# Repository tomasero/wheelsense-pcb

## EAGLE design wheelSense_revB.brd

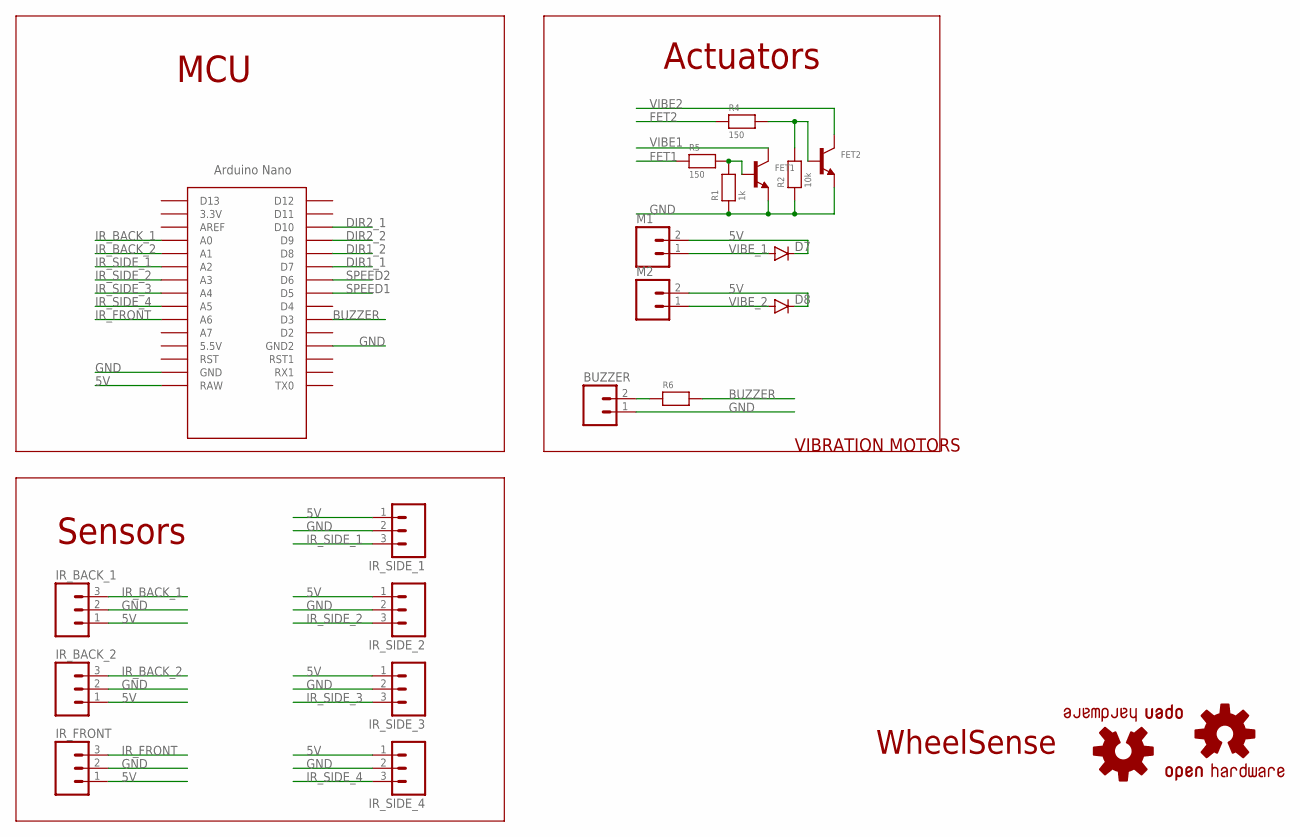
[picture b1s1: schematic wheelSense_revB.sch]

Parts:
BUZZER: M02POLAR; MOLEX-1X2
D7, D8: DIODESOD123; SOD-123
FET1, FET2: TRANSISTOR_NPN; SOT23-R
IR_BACK_1, IR_BACK_2: M03POLAR; MOLEX-1X3
IR_FRONT: M03POLAR; MOLEX-1X3
IR_SIDE_1, IR_SIDE_2, IR_SIDE_3, IR_SIDE_4: M03POLAR; MOLEX-1X3
LOGO1, LOGO2: OSHW-LOGOL-TOP; OSHW_LOGO_L_TOP
M1, M2: M02POLAR; MOLEX-1X2
R1: 1k; 0805
R2: 10k; 0805
R4, R5: 150; 0805
R6: RESISTOR0805; 0805
U$1: NANO

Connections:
5V: D7.C, D8.C, IR_BACK_1.1, IR_BACK_2.1, IR_FRONT.1, IR_SIDE_1.1, IR_SIDE_2.1, IR_SIDE_3.1, IR_SIDE_4.1, M1.2, M2.2, U$1.RAW
BUZZER: R6.2, U$1.D3
DIR1_1: U$1.D7
DIR1_2: U$1.D8
DIR2_1: U$1.D10
DIR2_2: U$1.D9
FET1: R5.1
FET2: R4.1
GND: BUZZER.1, FET1.2 (E), FET2.2 (E), IR_BACK_1.2, IR_BACK_2.2, IR_FRONT.2, IR_SIDE_1.2, IR_SIDE_2.2, IR_SIDE_3.2, IR_SIDE_4.2, R1.1, R2.1, U$1.GND, U$1.GND1 (GND2)
IR_BACK_1: IR_BACK_1.3, U$1.A0
IR_BACK_2: IR_BACK_2.3, U$1.A1
IR_FRONT: IR_FRONT.3, U$1.A6
IR_SIDE_1: IR_SIDE_1.3, U$1.A2
IR_SIDE_2: IR_SIDE_2.3, U$1.A3
IR_SIDE_3: IR_SIDE_3.3, U$1.A4
IR_SIDE_4: IR_SIDE_4.3, U$1.A5
unnamed: BUZZER.2, R6.1
unnamed: FET1.1 (B), R1.2, R5.2
unnamed: FET2.1 (B), R2.2, R4.2
SPEED1: U$1.D5
SPEED2: U$1.D6
VIBE1: FET1.3 (C)
VIBE2: FET2.3 (C)
VIBE_1: D7.A, M1.1
VIBE_2: D8.A, M2.1

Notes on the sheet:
MCU
Sensors
Actuators
WheelSense
VIBRATION MOTORS

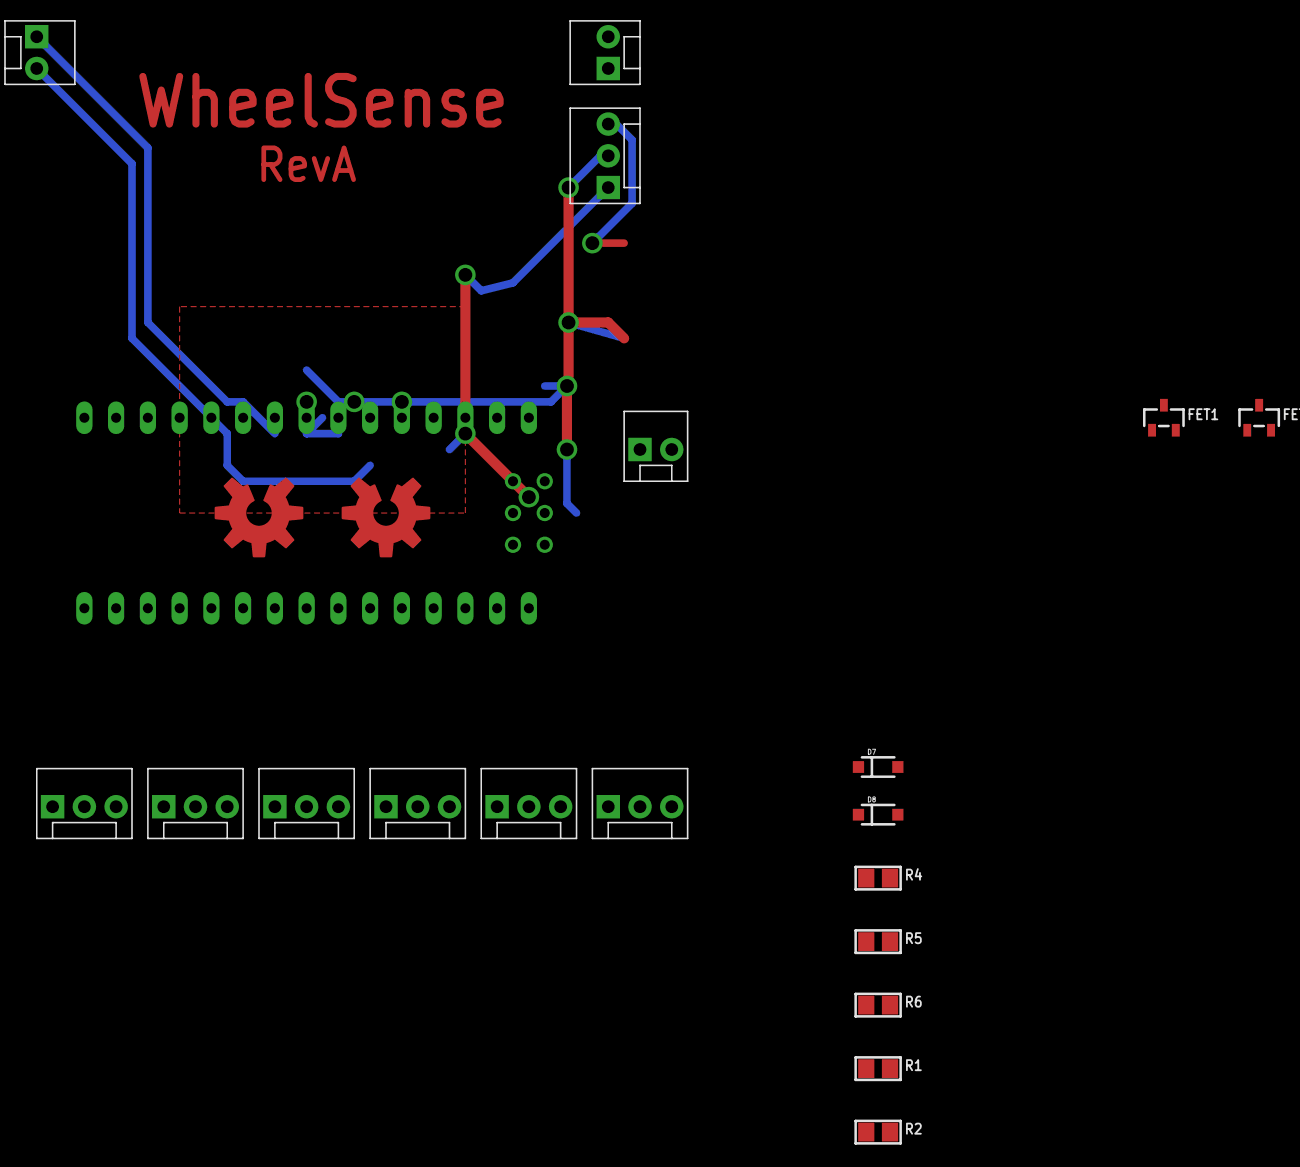
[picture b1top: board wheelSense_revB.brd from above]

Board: 2 copper layers, 22 parts (0 on the bottom side), 15 nets.

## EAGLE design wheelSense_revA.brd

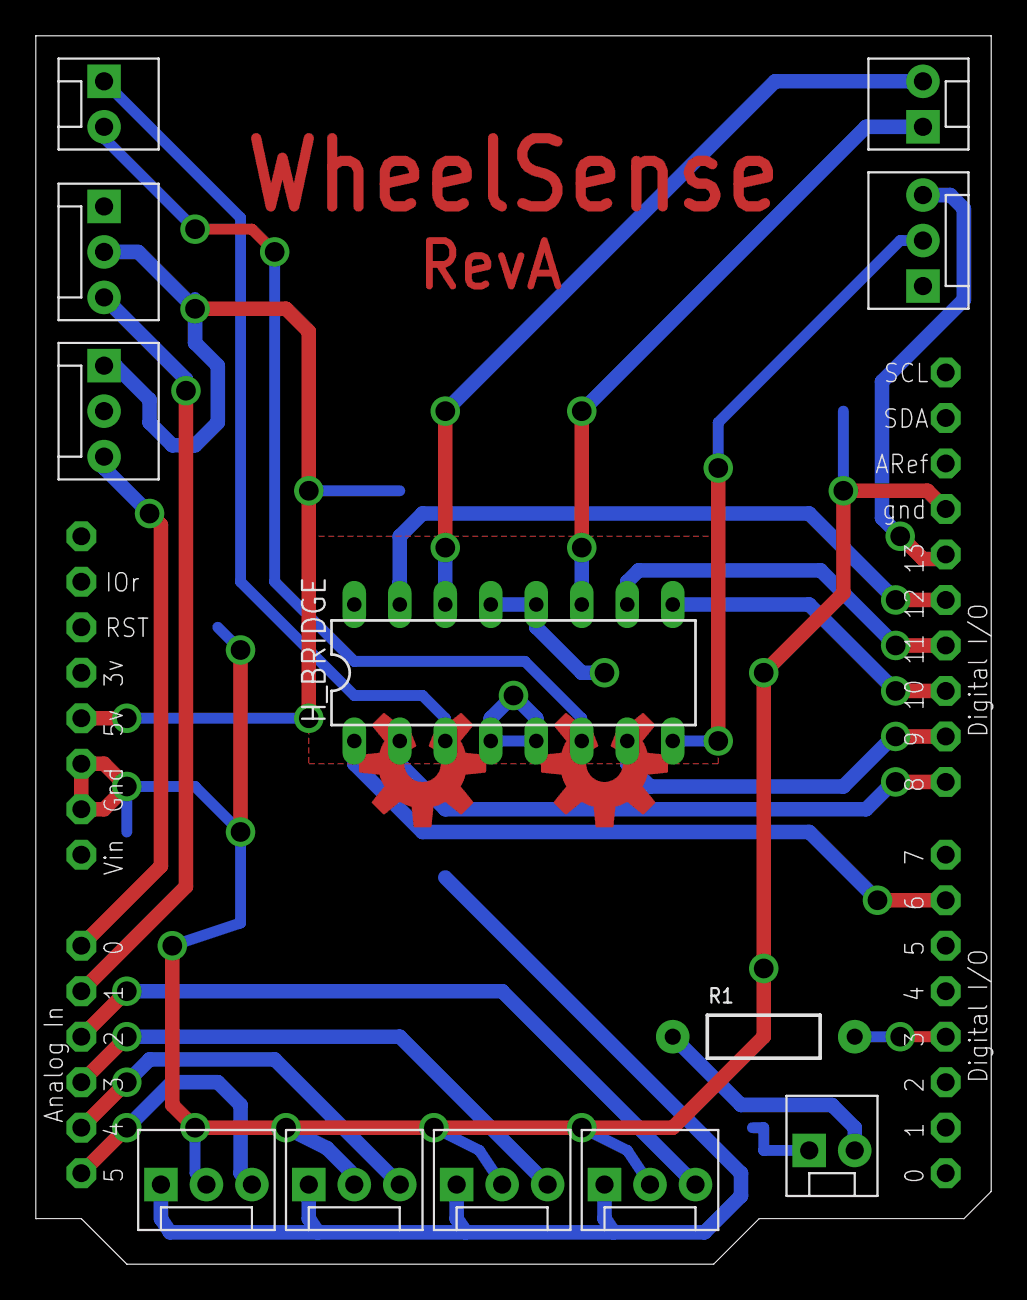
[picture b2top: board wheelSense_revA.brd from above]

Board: 2 copper layers, 53.3 x 68.6 mm, 15 parts (0 on the bottom side), 21 nets.

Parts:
H_BRIDGE: L293D; DIL16
IR_FRONT: MOLEX-1X3
IR_SIDE_1, IR_SIDE_2, IR_SIDE_3, IR_SIDE_4: MOLEX-1X3
JP8: MOLEX-1X2
LOGO1, LOGO2: OSHW-LOGOL-TOP; OSHW_LOGO_L_TOP
M1, M2: MOLEX-1X2
R1: AXIAL-0.4
U$1: ARDUIN0R3_NOHOLES; ARDUINOR3-NOHOLES
US_BACK_1, US_BACK_2: MOLEX-1X3

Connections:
5V: H_BRIDGE.8, H_BRIDGE.16, IR_FRONT.1, IR_SIDE_1.1, IR_SIDE_2.1, IR_SIDE_3.1, IR_SIDE_4.1, U$1.5V, US_BACK_1.2, US_BACK_2.2
BUZZER: R1.P$2, U$1.D3
DIR1_1: H_BRIDGE.2, U$1.D8
DIR1_2: H_BRIDGE.7, U$1.D9
DIR2_1: H_BRIDGE.10, U$1.D11
DIR2_2: H_BRIDGE.15, U$1.D12
GND: H_BRIDGE.4, H_BRIDGE.5, H_BRIDGE.12, H_BRIDGE.13, IR_FRONT.2, IR_SIDE_1.2, IR_SIDE_2.2, IR_SIDE_3.2, IR_SIDE_4.2, JP8.1, U$1.GND, U$1.GND1, U$1.GND2, US_BACK_1.1, US_BACK_2.1
IR_FRONT: IR_FRONT.3, U$1.A0
IR_SIDE_1: IR_SIDE_1.3, U$1.A2
IR_SIDE_2: IR_SIDE_2.3, U$1.A3
IR_SIDE_3: IR_SIDE_3.3, U$1.A4
IR_SIDE_4: IR_SIDE_4.3, U$1.A5
M1_1: H_BRIDGE.3, M1.1
M1_2: H_BRIDGE.6, M1.2
M2_1: H_BRIDGE.11, M2.1
M2_2: H_BRIDGE.14, M2.2
unnamed: JP8.2, R1.P$1
SPEED1: H_BRIDGE.1, U$1.D6
SPEED2: H_BRIDGE.9, U$1.D10
US_BACK_1: U$1.D13, US_BACK_1.3
US_BACK_2: U$1.A1, US_BACK_2.3

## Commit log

2017-03-14 revA
2017-03-14 upadted

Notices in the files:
parts and their libraries:
SparkFun-Connectors: Licensing: Creative Commons ShareAlike 4.0 International - https://creativecommons.org/licenses/by-sa/4.0
microbuilder: This work is placed in the public domain, and may be freely used for commercial and non-commercial work with the following conditions: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
